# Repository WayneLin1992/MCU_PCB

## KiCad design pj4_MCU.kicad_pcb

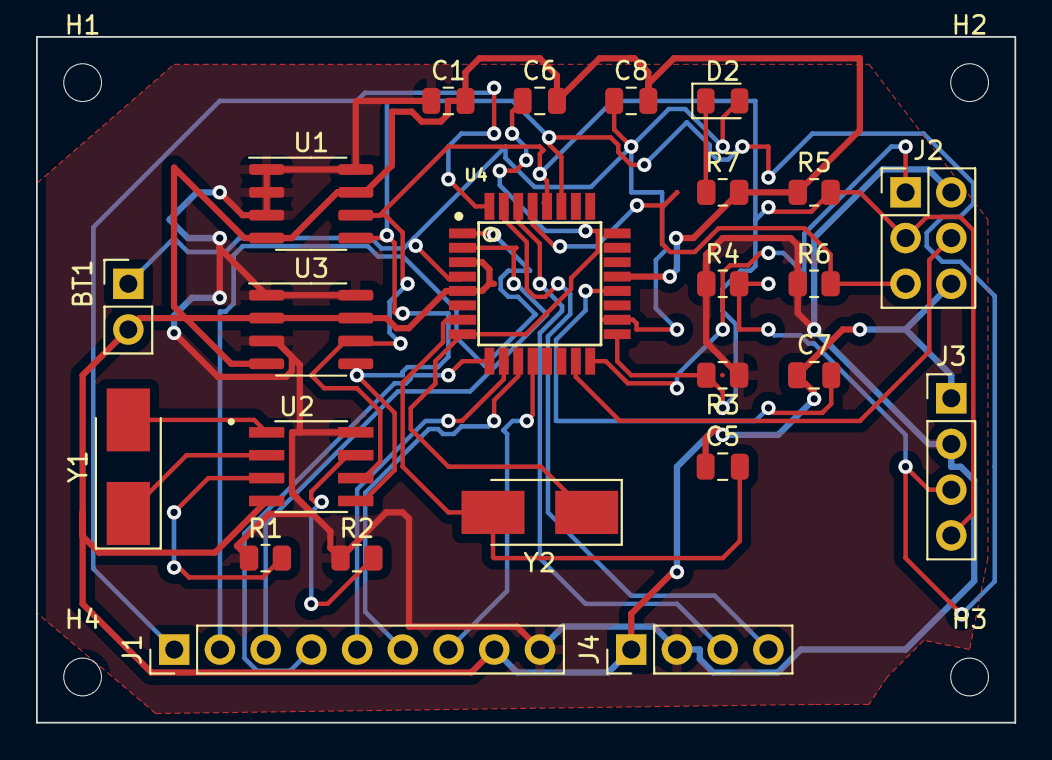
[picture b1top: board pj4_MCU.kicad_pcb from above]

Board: 2 copper layers, 54.4 x 38.1 mm, 28 parts (0 on the bottom side), 25 nets.

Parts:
BT1: Battery; PinHeader_1x02_P2.54mm_Vertical
C1, C7: 0.1uF; C_0805_2012Metric
C5, C6: 22pF; C_0805_2012Metric
C8: 100nF; C_0805_2012Metric
D2: LED; LED_0805_2012Metric
H1, H2, H3, H4: MountingHole; MountingHole_2.1mm
J1: Conn_01x09_Male; PinHeader_1x09_P2.54mm_Vertical
J2: Conn_02x03_Odd_Even; PinHeader_2x03_P2.54mm_Vertical
J3, J4: Conn_01x04_Male; PinHeader_1x04_P2.54mm_Vertical
R1, R2: 10k; R_0805_2012Metric
R3, R4: 4.7K; R_0805_2012Metric
R5, R7: 330; R_0805_2012Metric
R6: 10K; R_0805_2012Metric
U1, U3: 24LC1025; SOIC-8_3.9x4.9mm_P1.27mm
U2: DS1337S+; SOIC127P600X175-8N
U4: ATMEGA328P-AU; QFP80P900X900X120-32N
Y1: 32.768 KHz; Crystal_SMD_5032-2Pin_5.0x3.2mm_HandSoldering
Y2: 16 MHz; Crystal_SMD_5032-2Pin_5.0x3.2mm_HandSoldering

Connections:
/D2: J1.1, U4.32 (PD2)
/D3: J1.2, U4.1 (PD3)
/D4: J1.3, U4.2 (PD4)
/D5: J1.4, U4.9 (PD5)
/D6: J1.5, U4.10 (PD6)
/D7: J1.6, U4.11 (PD7)
/D8: J1.7, U4.12 (PB0)
/MISO: J2.1, U4.16 (PB4)
/MOSI: J2.4, U4.15 (PB3)
/RESET: J2.5, R6.2, U4.29 (PC6/~RESET)
/RX: J4.3, U4.30 (PD0)
/SCK: J2.3, J3.4, R3.2, R5.2, U1.6 (SCL), U2.6 (SCL), U3.6 (SCL), U4.17 (PB5), U4.28 (PC5)
/SDA: J3.3, R4.2, U1.5 (SDA), U2.5 (SDA), U3.5 (SDA), U4.27 (PC4)
/TX: J4.4, U4.31 (PD1)
/VCC: C1.1, J1.9, J2.2, J3.2, J4.2, R1.1, R2.1, R3.1, R4.1, R6.1, U1.1 (A0), U1.2 (A1), U1.3 (A2), U1.8 (VCC), U2.8 (VCC), U3.1 (A0), U3.3 (A2), U3.8 (VCC)
GND: BT1.2 (-), C1.2, C5.1, C6.2, C7.1, C8.2, J1.8, J2.6, J3.1, J4.1, R5.1, R7.2, U1.4 (GND), U1.7 (WP), U2.4 (GND), U3.2 (A1), U3.4 (GND), U3.7 (WP), U4.3 (GND), U4.5 (GND), U4.21 (GND)
unnamed: D2.1 (K), R7.1
unnamed: U2.1 (X1), Y1.2
unnamed: U2.2 (X2), Y1.1
unnamed: R1.2, U2.3 (~INTA)
unnamed: R2.2, U2.7 (SQW/~INT)
unnamed: C5.2, U4.7 (PB6), Y2.2
unnamed: BT1.1 (+), C8.1, D2.2 (A), U4.4 (VCC), U4.18 (AVCC)
unnamed: C7.2, U4.20 (AREF)
unnamed: C6.1, U4.8 (PB7), Y2.1

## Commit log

2022-01-07 MCU_PCB
2022-01-07 gerber
    plot gerber
2022-01-07 add pro and prl
    add pro and prl
